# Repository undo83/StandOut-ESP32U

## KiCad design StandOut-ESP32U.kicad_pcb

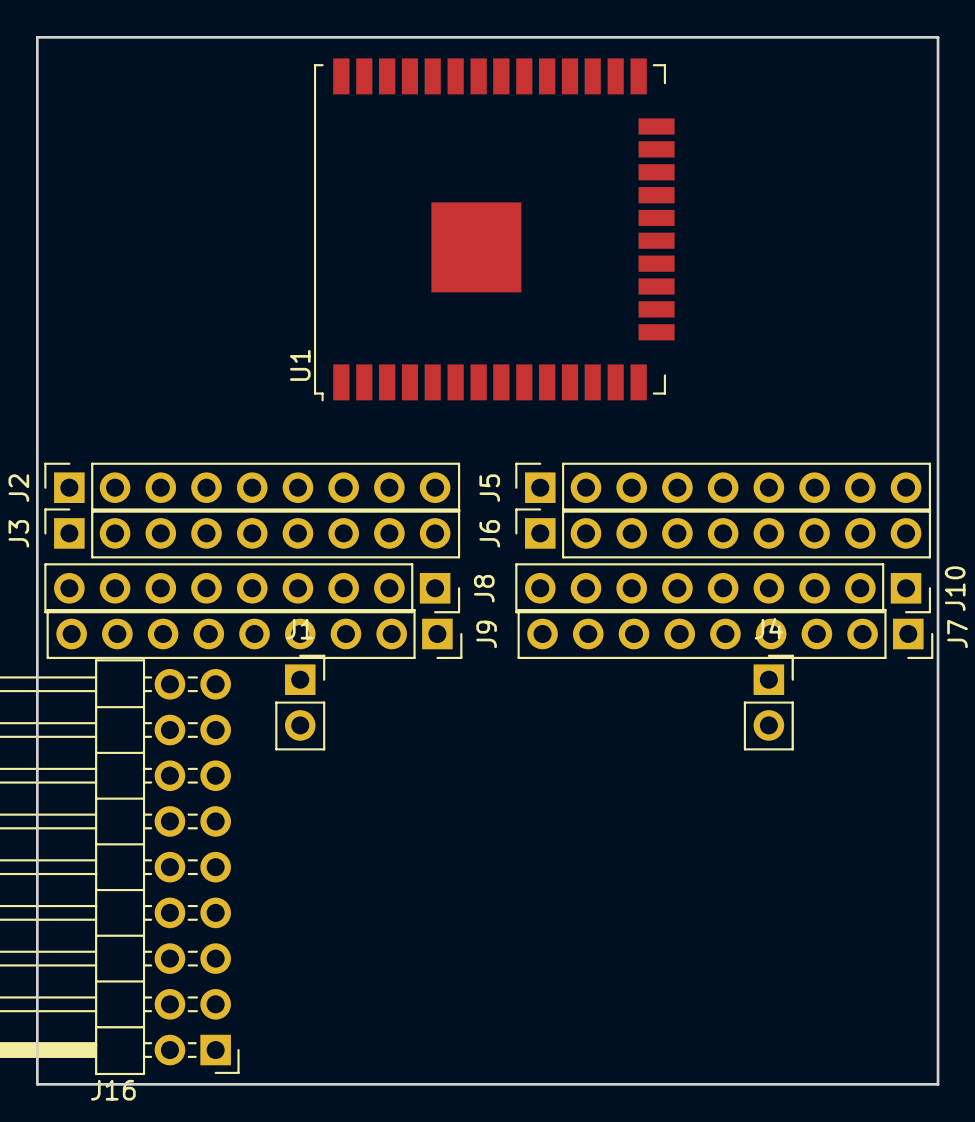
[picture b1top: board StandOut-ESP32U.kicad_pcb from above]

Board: 4 copper layers, 50.0 x 58.2 mm, 12 parts (0 on the bottom side), 29 nets, no tracks yet.

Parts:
J1: UART_2; PinSocket_1x02_P2.54mm_Vertical
J2, J5, J7, J9: GPIO; PinSocket_1x09_P2.54mm_Vertical
J3, J6, J8, J10: Common Pins; PinSocket_1x09_P2.54mm_Vertical
J4: UART_0; PinSocket_1x02_P2.54mm_Vertical
J16: Conn_01x18_Male; PinHeader_2x09_P2.54mm_Horizontal
U1: ESP32-WROOM-32U

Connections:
+3.3V: J3.1, J6.1, J8.1, J10.1, J16.1
+5V: J3.9, J6.9, J8.9, J10.9, J16.17
ADC1_CH0: J2.9, J7.9, J16.18, U1.4
ADC1_CH3: J2.8, J7.8, J16.16, U1.5
ADC1_CH4: J5.6, J9.6, U1.8
ADC1_CH5: J5.7, J9.7, U1.9
ADC1_CH6: J5.8, J9.8, U1.6
ADC1_CH7: J5.9, J9.9, U1.7
ADC2_CH0: J2.2, J7.2, J16.4, U1.26
ADC2_CH1: J2.3, J7.3, J16.6, U1.25
ADC2_CH2: J5.2, J9.2, U1.24
ADC2_CH3: J2.7, J7.7, J16.14, U1.23
ADC2_CH4: J2.5, J7.5, J16.10, U1.16
ADC2_CH5: J2.4, J7.4, J16.8, U1.14
ADC2_CH6: J2.6, J7.6, J16.12, U1.13
ADC2_CH7: J5.3, J9.3, U1.12
ADC2_CH8: J2.1, J5.4, J7.1, J9.4, J16.2, U1.10
ADC2_CH9: J5.1, J5.5, J9.1, J9.5, U1.11
GND: J3.2, J6.2, J8.2, J10.2, J16.3, U1.1, U1.15, U1.38
I2C_SCL: J3.8, J6.8, J8.8, J10.8, J16.15, U1.36
I2C_SDA: J3.7, J6.7, J8.7, J10.7, J16.13, U1.33
IO1: J4.1, U1.35
IO3: J4.2, U1.34
IO5: J3.6, J6.6, J8.6, J10.6, J16.11, U1.29
IO16: J1.2, U1.27
IO17: J1.1, U1.28
IO18: J3.5, J6.5, J8.5, J10.5, J16.9, U1.30
IO19: J3.3, J6.3, J8.3, J10.3, J16.5, U1.31
IO23: J3.4, J6.4, J8.4, J10.4, J16.7, U1.37

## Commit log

2019-01-22 Working on positioning
2019-01-22 Working on Schematic - Micro-USB & UART
